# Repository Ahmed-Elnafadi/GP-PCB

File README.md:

# GP-PCB
This PCB is used to connect all Electrical signals and power in UAV Project.

# Real PCB

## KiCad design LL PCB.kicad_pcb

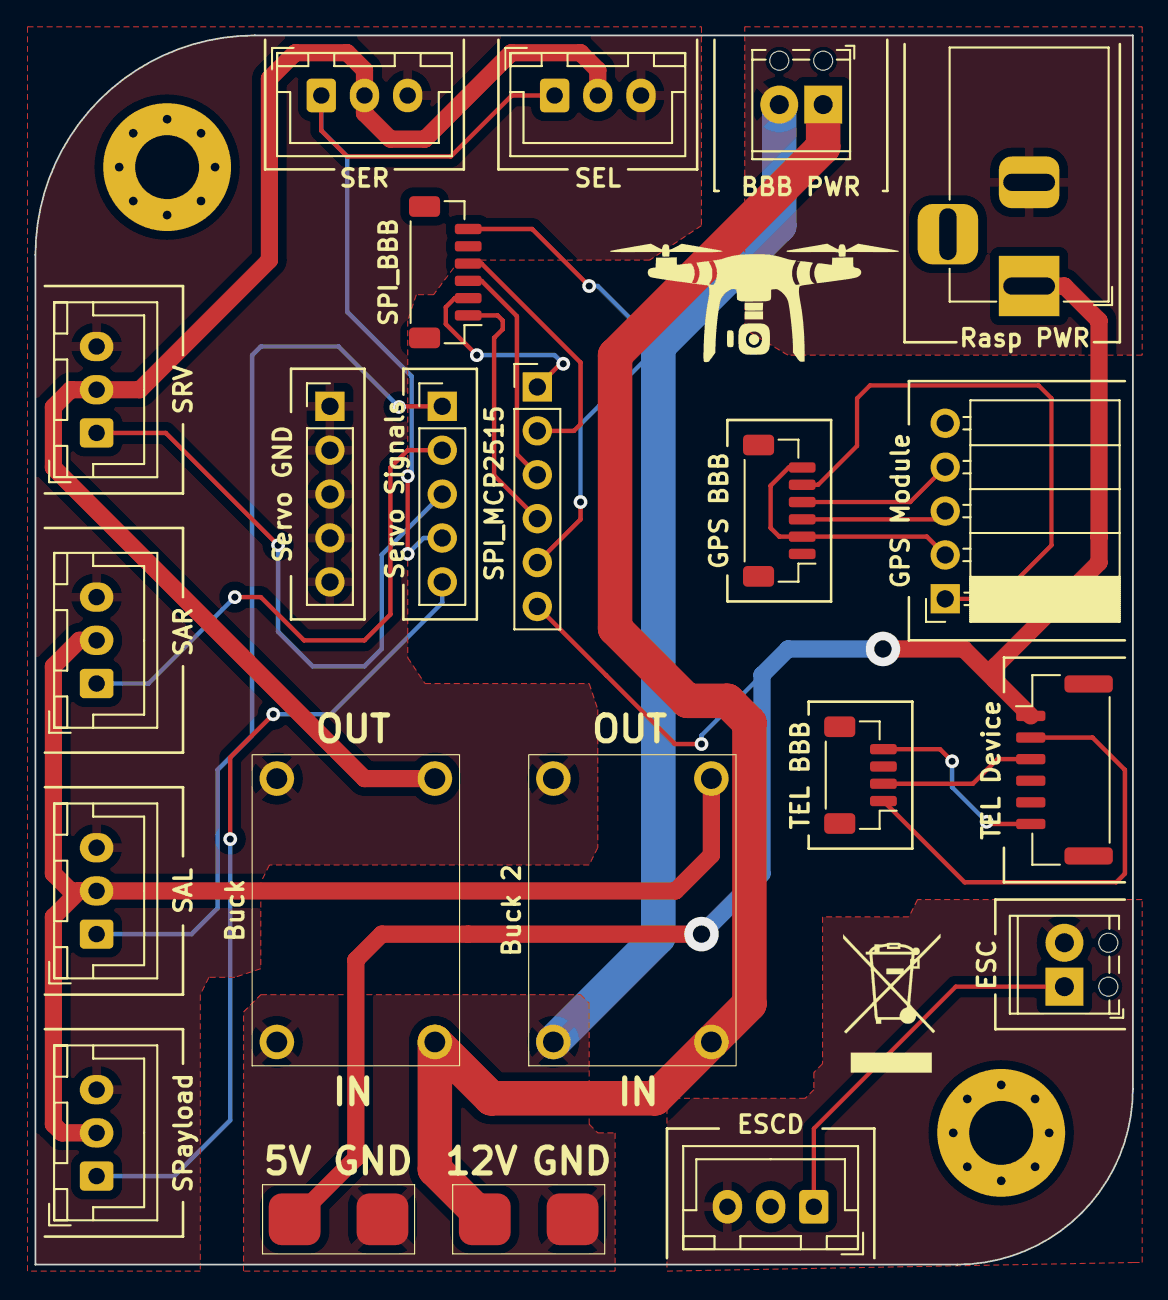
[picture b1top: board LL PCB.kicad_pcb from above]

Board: 2 copper layers, 63.5 x 71.1 mm, 22 parts (0 on the bottom side), 24 nets.

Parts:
BBB PWR: Beagle PWR; TerminalBlock_Phoenix_MPT-0,5-2-2.54_1x02_P2.54mm_Horizontal
Buck: mini_360
Buck 2: mini_360
ESC: STM32-ESC-SIGNAL; TerminalBlock_Phoenix_MPT-0,5-2-2.54_1x02_P2.54mm_Horizontal
ESCD: ESC-Device; JST_XH_B3B-XH-A_1x03_P2.50mm_Vertical
GPS BBB: JST-SH 1mm GPS-BBB; JST_SH_BM06B-SRSS-TB_1x06-1MP_P1.00mm_Vertical
GPS Module: JST 2.5mm GPS Module; PinSocket_1x05_P2.54mm_Horizontal
J3: +5V Input; PWR_Pad
J4: +12V Input; PWR_Pad
Rasp PWR: Raspberry PWR; BarrelJack_Horizontal
SAL: Servo-Annulus-Left; JST_XH_B3B-XH-A_1x03_P2.50mm_Vertical
SAR: Servo-Annulus-Right; JST_XH_B3B-XH-A_1x03_P2.50mm_Vertical
SEL: Servo-Elevator-Left; JST_XH_B3B-XH-A_1x03_P2.50mm_Vertical
SER: Servo-Elevator-Right; JST_XH_B3B-XH-A_1x03_P2.50mm_Vertical
SPI_BBB: SPI_BBB; JST_SH_BM06B-SRSS-TB_1x06-1MP_P1.00mm_Vertical
SPI_MCP2515: SPI_MCP2515; PinHeader_1x06_P2.54mm_Vertical
SPayload: Servo-Payload; JST_XH_B3B-XH-A_1x03_P2.50mm_Vertical
SRV: Servo-Rudder-Vertical; JST_XH_B3B-XH-A_1x03_P2.50mm_Vertical
Servo GND: Servo-GND-IN; PinHeader_1x05_P2.54mm_Vertical
Servo Signals: Servo-Signals-IN; PinHeader_1x05_P2.54mm_Vertical
TEL BBB: TEL-BBB JST-SH 1mm; JST_SH_BM04B-SRSS-TB_1x04-1MP_P1.00mm_Vertical
TEL Device: TEL-Device; JST_GH_BM06B-GHS-TBT_1x06-1MP_P1.25mm_Vertical

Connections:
6V-1: Buck.3 (PWR_OUT), SEL.2, SER.2, SRV.2
6V-2: Buck 2.3 (PWR_OUT), SAL.2, SAR.2, SPayload.2
+5V: J3.1, Rasp PWR.1, SPI_MCP2515.6, TEL Device.1
+12V: BBB PWR.1, Buck.1 (PWR_IN), Buck 2.1 (PWR_IN), J4.1
CS: SPI_BBB.1, SPI_MCP2515.4
ESC-GND: ESC.2, ESCD.3
ESC-SIG: ESC.1, ESCD.1
GND: BBB PWR.2, Buck.2 (GND_IN), Buck 2.2 (GND_IN), J3.2, J4.2, Rasp PWR.2, SPI_BBB.6, SPI_MCP2515.5
GND1: GPS BBB.2, GPS BBB.6, GPS Module.2
GND2: TEL BBB.4, TEL Device.6
GNDA: Buck.4 (GND_OUT), Buck 2.4 (GND_OUT), SAL.3, SAR.3, SEL.3, SER.3, SPayload.3, SRV.3, Servo GND.1, Servo GND.2, Servo GND.3, Servo GND.4, Servo GND.5
GPS-RX: GPS BBB.4, GPS Module.4
GPS-TX: GPS BBB.3, GPS Module.3
GPS-VCC: GPS BBB.5, GPS Module.1
MISO: SPI_BBB.3, SPI_MCP2515.3
MOSI: SPI_BBB.4, SPI_MCP2515.2
SAL: SAL.1, Servo Signals.1
SAR: SAR.1, Servo Signals.2
SCK: SPI_BBB.2, SPI_MCP2515.1
SEH: SEL.1, SER.1, Servo Signals.4
SP: SPayload.1, Servo Signals.5
SRV: SRV.1, Servo Signals.3
TEL-RX: TEL BBB.2, TEL Device.3
TEL-TX: TEL BBB.1, TEL Device.2

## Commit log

2024-07-05 Add PCB Files to remote repo.
2024-07-05 Rename 20240623_003441.jpg to Real PCB.jpg
